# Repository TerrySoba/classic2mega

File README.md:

# Classic2mega

This adapter allows the usage of Nintendo Wii Classic Controllers with a Sega Megadrive/Genesis.
Although it is called classic2mega (for megadrive) it also works with other systems that use the same connector like the Commodore Amiga.

It also has a mode to use a Classic Controller as an Amiga mouse.

## Supported input devices
 * Nintendo Classic Controller
 * Nintendo Classic Controller Pro
 * Super Nintendo Mini Controller
 * NES Mini Controller
 
## Adapter Modes
 * Megadrive / Genesis Mode
 * Jump And Run Mode
 * Amiga Mouse Mode
 * Delay Mode

[Building Instructions (german)](doc/building_instructions_de.md)

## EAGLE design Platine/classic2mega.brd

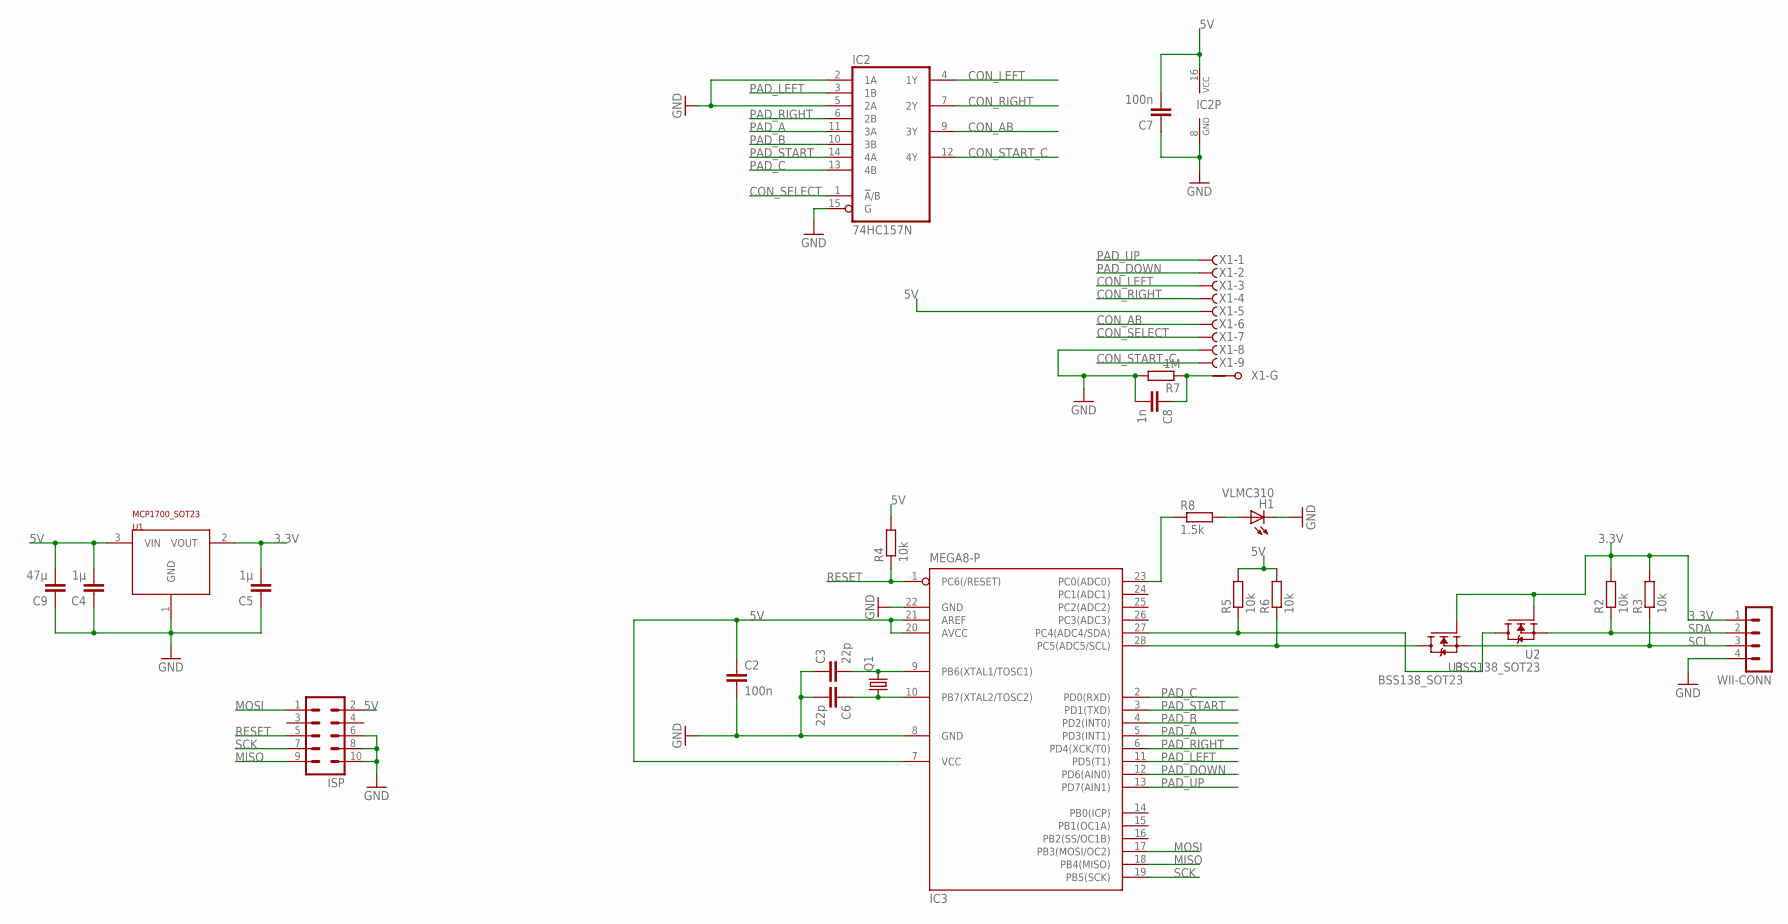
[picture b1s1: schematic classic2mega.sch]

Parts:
C2, C7: 100n; C0805K
C3, C6: 22p; C0805K
C4, C5: 1µ; C0805K
C8: 1n; C0805K
C9: 47µ; C1210
H1: VLMC310; PLCC-2
IC2: 74HC157N; DIL16
IC3: MEGA8-P; DIL28-3
ISP: MA05-2
Q1: CRYSTALHC49S; HC49/S
R2, R3, R4, R5, R6: 10k; M0805
R7: 1M; M0805
R8: 1.5k; M0805
U1: MCP1700_SOT23; SOT23
U2, U3: BSS138_SOT23; SOT23
WII-CONN: MA04-1
X1: F09HPS; F09HP

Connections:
3.3V: C5.2, R2.2, R3.2, U1.2 (VOUT), U2.1 (G), U3.1 (G), WII-CONN.1
5V: C2.1, C4.2, C7.2, C9.2, IC2.16 (VCC), IC3.7 (VCC), IC3.20 (AVCC), IC3.21 (AREF), ISP.2, R4.2, R5.2, R6.2, U1.3 (VIN), X1.5 (F)
CON_AB: IC2.9 (3Y), X1.6 (F)
CON_LEFT: IC2.4 (1Y), X1.3 (F)
CON_RIGHT: IC2.7 (2Y), X1.4 (F)
CON_SELECT: IC2.1 (!A!/B), X1.7 (F)
CON_START_C: IC2.12 (4Y), X1.9 (F)
GND: C2.2, C3.1, C4.1, C5.1, C6.2, C7.1, C8.2, C9.1, H1.C, IC2.2 (1A), IC2.5 (2A), IC2.8 (GND), IC2.15 (G), IC3.8 (GND), IC3.22 (GND), ISP.6, ISP.8, ISP.10, R7.2, U1.1 (GND), WII-CONN.4, X1.8 (F)
MISO: IC3.18 (PB4(MISO)), ISP.9
MOSI: IC3.17 (PB3(MOSI/OC2)), ISP.1
unnamed: IC3.27 (PC4(ADC4/SDA)), R5.1, U2.3 (D)
unnamed: IC3.23 (PC0(ADC0)), R8.1
unnamed: C3.2, IC3.9 (PB6(XTAL1/TOSC1)), Q1.2
unnamed: IC3.28 (PC5(ADC5/SCL)), R6.1, U3.3 (D)
unnamed: C6.1, IC3.10 (PB7(XTAL2/TOSC2)), Q1.1
unnamed: C8.1, R7.1, X1.G1
unnamed: H1.A, R8.2
PAD_A: IC2.11 (3A), IC3.5 (PD3(INT1))
PAD_B: IC2.10 (3B), IC3.4 (PD2(INT0))
PAD_C: IC2.13 (4B), IC3.2 (PD0(RXD))
PAD_DOWN: IC3.12 (PD6(AIN0)), X1.2 (F)
PAD_LEFT: IC2.3 (1B), IC3.11 (PD5(T1))
PAD_RIGHT: IC2.6 (2B), IC3.6 (PD4(XCK/T0))
PAD_START: IC2.14 (4A), IC3.3 (PD1(TXD))
PAD_UP: IC3.13 (PD7(AIN1)), X1.1 (F)
RESET: IC3.1 (PC6(/RESET)), ISP.5, R4.1
SCK: IC3.19 (PB5(SCK)), ISP.7
SCL: R3.1, U3.2 (S), WII-CONN.3
SDA: R2.1, U2.2 (S), WII-CONN.2

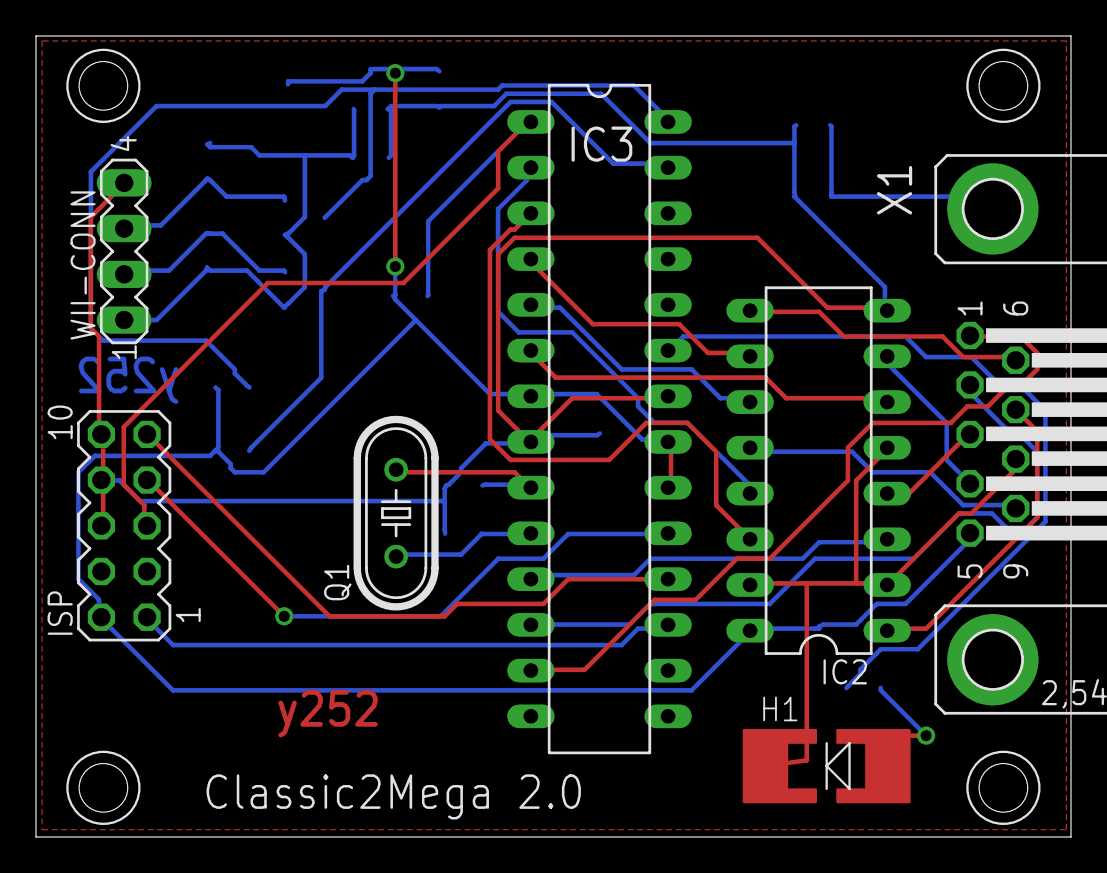
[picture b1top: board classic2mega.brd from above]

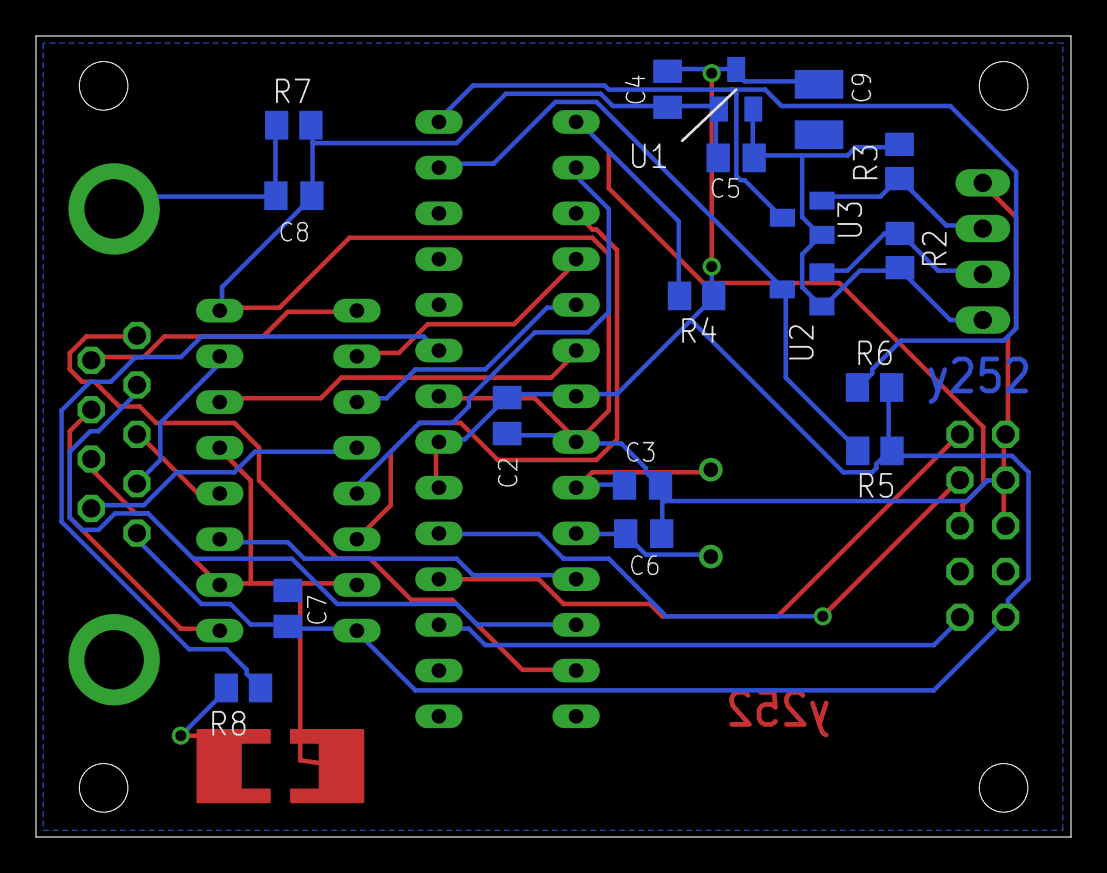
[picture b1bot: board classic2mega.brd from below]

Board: 2 copper layers, 57.5 x 44.5 mm, 26 parts (18 on the bottom side), 29 nets.

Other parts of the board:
U$6: G028-HOLES

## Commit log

2015-06-27 Initial import
2015-06-27 Add "y252" string to backside copper
2015-06-27 Version used for first pcb-production
2015-07-12 press x to light led
2015-07-12 Works now :)
2015-09-05 Add clean target to makefile
2015-09-05 Add jump and run mode
2017-12-27 Add delay mode
2018-04-02 Add gitignore and eclipse project files
2018-04-02 Add experimental amiga mouse support
2018-06-02 Working version
2018-06-03 Fix button mapping in jumn and run mode
2018-06-05 Add BOM
2018-06-05 Fix BOM
2018-06-10 Add symbols to BOM
2018-06-10 New board revison
2018-06-10 Remove unneeded components
2018-06-10 Add reichelt part list
2018-06-13 Add programming adapter link
2018-06-15 Add images of PCB
2018-07-07 Add commented out line for usbasp
2018-07-08 Add bss138 lib
2018-07-08 Replace i2c level shifter with discrete components
2018-07-08 Change ICs to DIP packages
2018-07-08 Change C9 to 1210 footprint
2018-07-08 Remove signal lines under crystal
2018-07-08 Move 100nf closer to 5v of ic
2018-07-08 Stuff
2018-07-19 Change to atmega8 and 8MHz internal oscillator
2018-07-21 Update BOM
2018-07-26 Blink LED at startup
2018-07-26 Add PCB link
2018-07-26 Add photos of PCB
2018-07-26 Add missing parts to list
2020-05-03 Add docker build containe
